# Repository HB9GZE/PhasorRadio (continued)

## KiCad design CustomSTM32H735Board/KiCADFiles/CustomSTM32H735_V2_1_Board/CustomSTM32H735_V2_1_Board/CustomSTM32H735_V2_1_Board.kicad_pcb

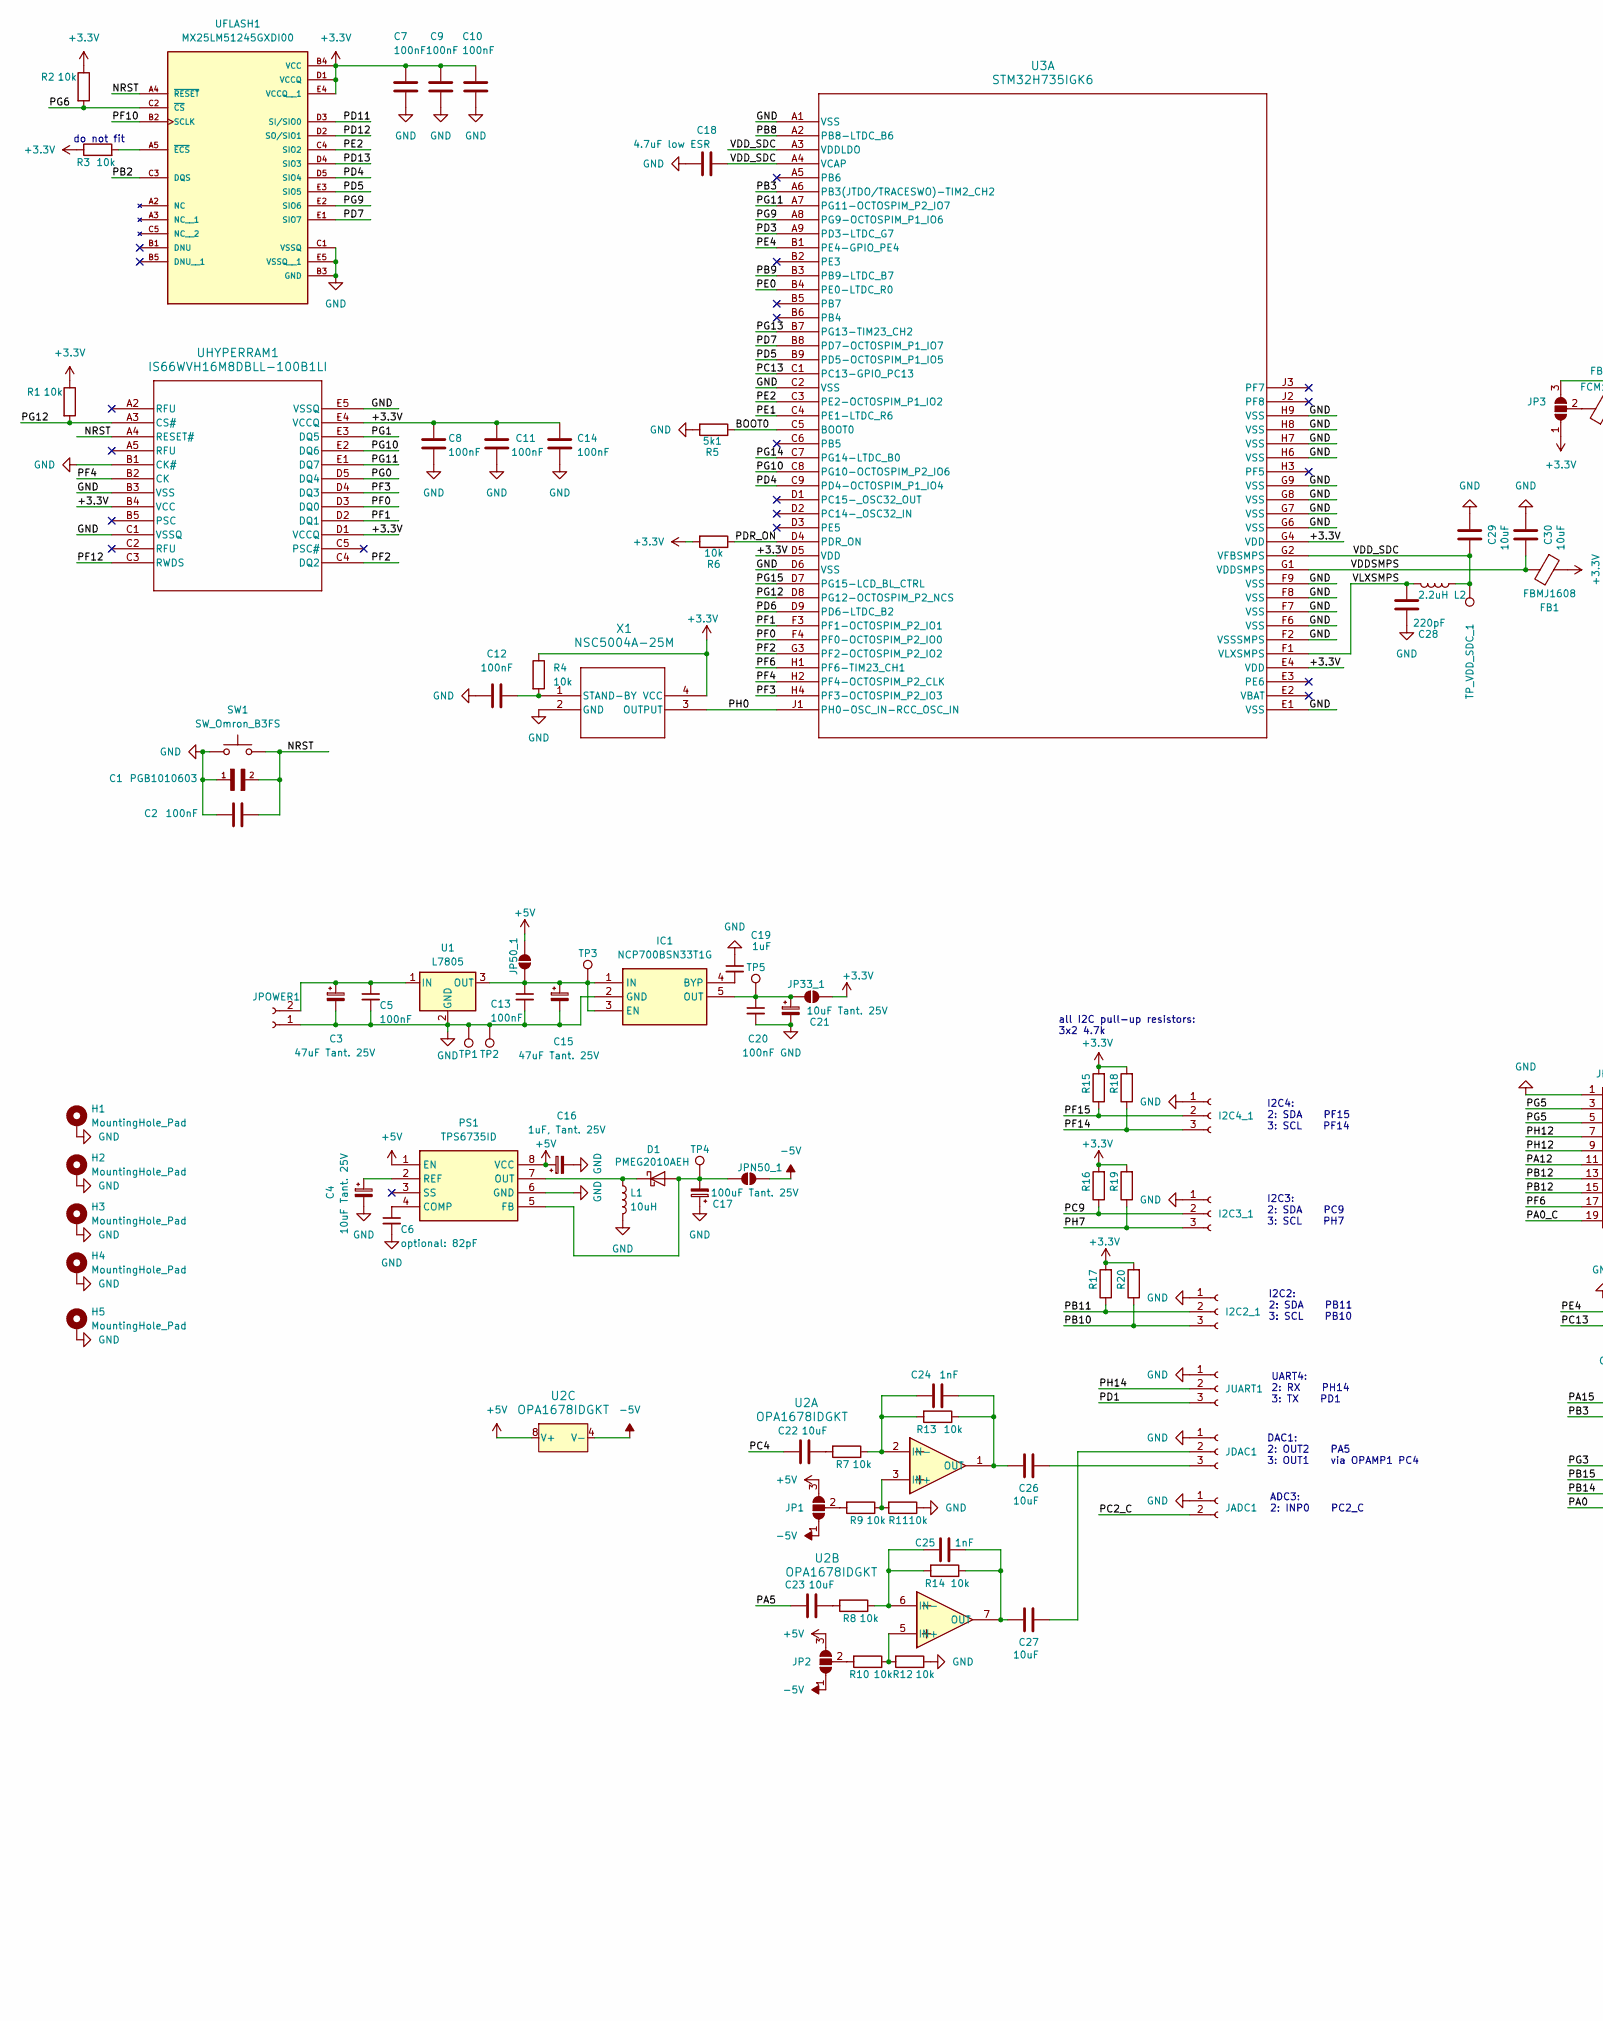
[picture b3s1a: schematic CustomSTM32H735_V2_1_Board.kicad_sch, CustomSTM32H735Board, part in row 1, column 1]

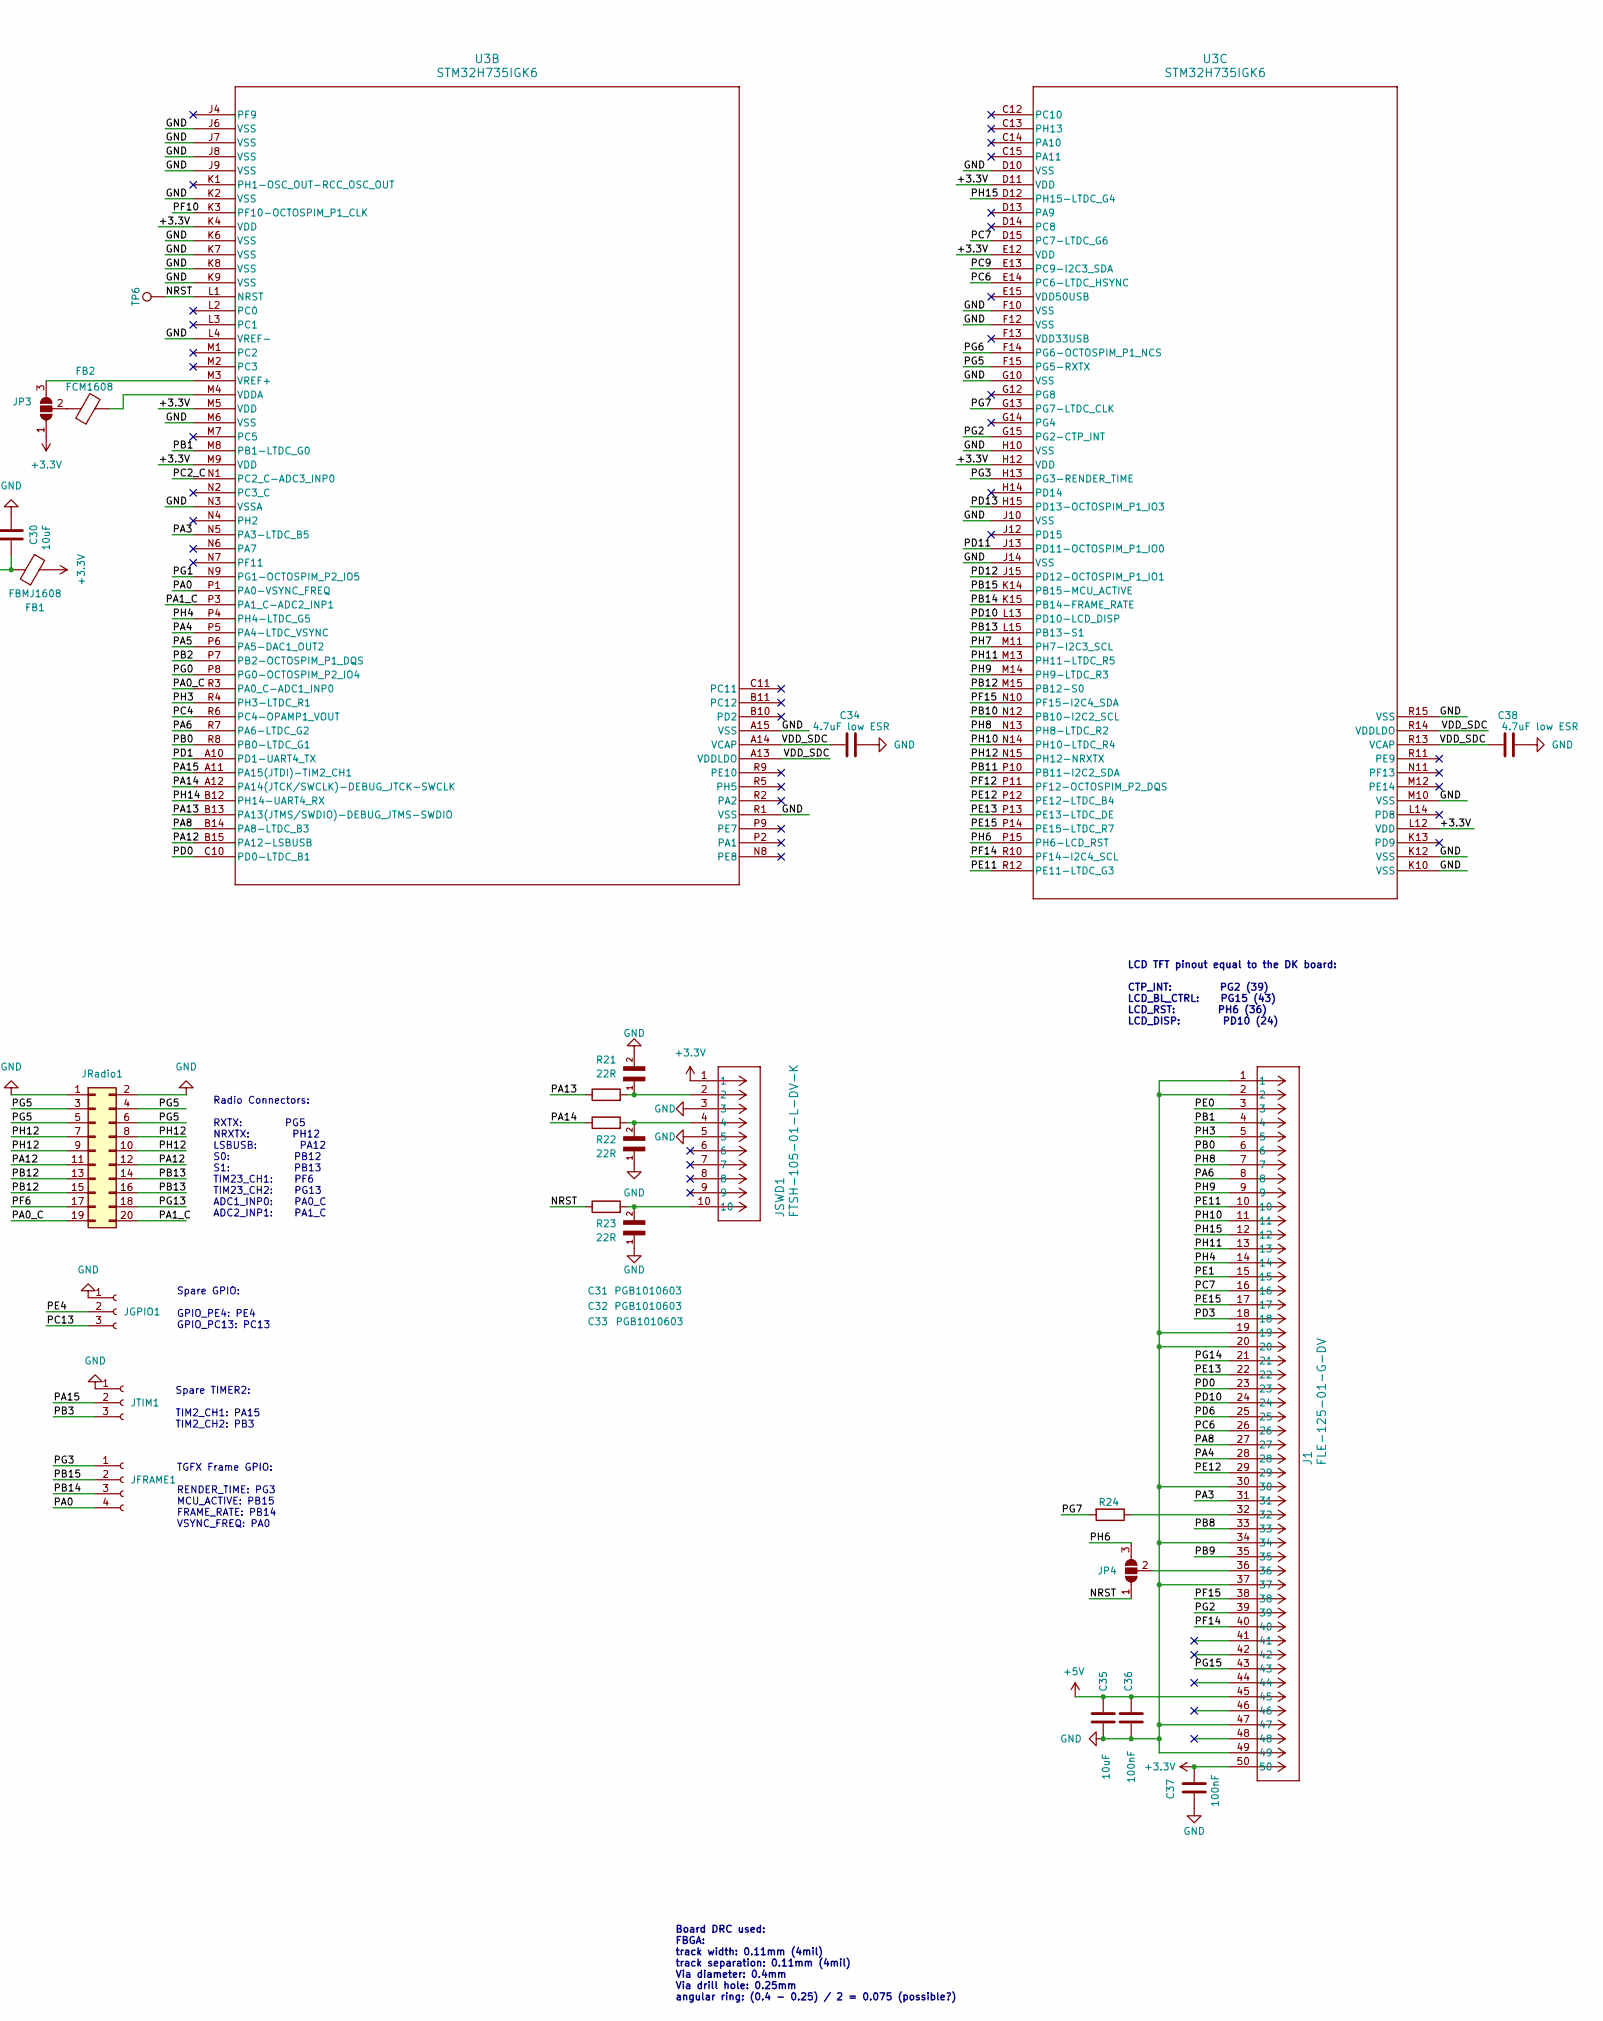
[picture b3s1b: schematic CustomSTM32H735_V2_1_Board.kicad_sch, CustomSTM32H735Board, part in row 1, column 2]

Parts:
C1, C31, C32, C33: PGB1010603; C_0603_1608Metric
C2, C5, C7, C8, C9, C10, C11, C12, C13, C14, C20, C36, C37: 100nF; C_0805_2012Metric_Pad1.18x1.45mm_HandSolder
C3, C15: 47uF Tant. 25V; CP_EIA-6032-20_AVX-F_Pad2.25x2.35mm_HandSolder
C4, C21: 10uF Tant. 25V; CP_EIA-6032-20_AVX-F_Pad2.25x2.35mm_HandSolder
C6: optional: 82pF; C_0805_2012Metric_Pad1.18x1.45mm_HandSolder
C16: 1uF, Tant. 25V; CP_EIA-6032-20_AVX-F_Pad2.25x2.35mm_HandSolder
C17: 100uF Tant. 25V; CP_EIA-6032-20_AVX-F_Pad2.25x2.35mm_HandSolder
C18, C34, C38: 4.7uF low ESR; C_0805_2012Metric_Pad1.18x1.45mm_HandSolder
C19: 1uF; C_0805_2012Metric_Pad1.18x1.45mm_HandSolder
C22, C23, C26, C27, C29, C30, C35: 10uF; C_0805_2012Metric_Pad1.18x1.45mm_HandSolder
C24, C25: 1nF; C_0805_2012Metric_Pad1.18x1.45mm_HandSolder
C28: 220pF; C_0805_2012Metric_Pad1.18x1.45mm_HandSolder
D1: PMEG2010AEH; D_SOD-123F
FB1: FBMJ1608; L_0603_1608Metric_Pad1.05x0.95mm_HandSolder
FB2: FCM1608; L_0603_1608Metric_Pad1.05x0.95mm_HandSolder
H1, H2, H3, H4, H5: MountingHole_Pad; MountingHole_3.2mm_M3_Pad_TopBottom
I2C2_1, I2C3_1, I2C4_1: Conn_01x03_Socket; JST_XH_B3B-XH-A_1x03_P2.50mm_Vertical
IC1: NCP700BSN33T1G; SOT95P275X120-5N; Manufacturer_Part_Number NCP700BSN33T1G; Mouser Part Number 863-NCP700BSN33T1G
J1: FLE-125-01-G-DV; CON50_2X25_UF_FLE_SAI
JADC1: Conn_01x02_Socket; JST_XH_B2B-XH-A_1x02_P2.50mm_Vertical
JDAC1: Conn_01x03_Socket; JST_XH_B3B-XH-A_1x03_P2.50mm_Vertical
JFRAME1: Conn_01x04_Socket; JST_XH_B4B-XH-A_1x04_P2.50mm_Vertical
JGPIO1: Conn_01x03_Socket; JST_XH_B3B-XH-A_1x03_P2.50mm_Vertical
JP1, JP2, JP3, JP4: SolderJumper_3_Open; SolderJumper-3_P1.3mm_Open_Pad1.0x1.5mm_NumberLabels
JP33_1, JP50_1: SolderJumper_2_Open; SolderJumper-2_P1.3mm_Open_Pad1.0x1.5mm
JPN50_1: SolderJumper_2_Open; SolderJumper-2_P1.3mm_Open_Pad1.0x1.5mm
JPOWER1: Conn_01x02_Socket; JST_XH_B2B-XH-A_1x02_P2.50mm_Vertical
JRadio1: Conn_02x10_Odd_Even; IDC-Header_2x10_P2.54mm_Vertical
JSWD1: FTSH-105-01-L-DV-K; CON10_2X5_DUK_FTSH_SAI-M
JTIM1: Conn_01x03_Socket; JST_XH_B3B-XH-A_1x03_P2.50mm_Vertical
JUART1: Conn_01x03_Socket; JST_XH_B3B-XH-A_1x03_P2.50mm_Vertical
L1: 10uH; L_1812_4532Metric_Pad1.30x3.40mm_HandSolder
L2: 2.2uH; L_Murata_DFE201610P
PS1: TPS6735ID; SOIC127P600X175-8N; Manufacturer_Part_Number TPS6735ID; Mouser Part Number 595-TPS6735ID
R1, R2, R3, R4, R6, R7, R8, R9, R10, R11, R12, R13, R14: 10k; R_0805_2012Metric_Pad1.20x1.40mm_HandSolder
R5: 5k1; R_0805_2012Metric_Pad1.20x1.40mm_HandSolder
R15, R16, R17, R18, R19, R20: 4.7k; R_0805_2012Metric_Pad1.20x1.40mm_HandSolder
R21, R22, R23: 22R; R_0805_2012Metric_Pad1.20x1.40mm_HandSolder
R24: 0R; R_0805_2012Metric_Pad1.20x1.40mm_HandSolder
SW1: SW_Omron_B3FS; SW_SPST_Omron_B3FS-100xP
TP1, TP2, TP3, TP4, TP5, TP6: TestPoint; Pin_D0.7mm_L6.5mm_W1.8mm_FlatFork
TP_VDD_SDC_1: TestPoint; Pin_D0.7mm_L6.5mm_W1.8mm_FlatFork
U1: L7805; TO-220-3_Horizontal_TabDown_GND_Pad
U2: OPA1678IDGKT; OPA1678_L
U3: STM32H735IGK6; BGA_735IGK6_STM
UFLASH1: MX25LM51245GXDI00; BGA24C100P5X5_600X800X120; PARTREV 1.1
UHYPERRAM1: IS66WVH16M8DBLL-100B1LI; TFBGA24_6X8_ISI
X1: NSC5004A-25M; NSC5004_NDK

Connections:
+3.3V: C7.1, C8.1, C9.1, C10.1, C11.1, C14.1, C37.1, FB1.1, J1.50, JP3.1 (A), JP33_1.2 (B), JSWD1.1, R1.1, R2.1, R3.1, R4.1, R6.2, R15.2, R16.2, R17.2, R18.2, R19.2, R20.2, U3.D5 (VDD), U3.D11 (VDD), U3.E4 (VDD), U3.E12 (VDD), U3.G4 (VDD), U3.H12 (VDD), U3.K4 (VDD), U3.L12 (VDD), U3.M5 (VDD), U3.M9 (VDD), UFLASH1.B4 (VCC), UFLASH1.D1 (VCCQ), UFLASH1.E4 (VCCQ__1), UHYPERRAM1.B4 (VCC), UHYPERRAM1.D1 (VCCQ), UHYPERRAM1.E4 (VCCQ), X1.4 (VCC)
+5V: C16.1, C35.1, C36.1, J1.45, JP1.3 (B), JP2.3 (B), JP50_1.2 (B), PS1.1 (EN), PS1.8 (VCC), U2.8 (V+)
-5V: JP1.1 (A), JP2.1 (A), JPN50_1.2 (B), U2.4 (V-)
/BOOT0: R5.1, U3.C5 (BOOT0)
/NRST: C1.2, C2.1, JP4.1 (A), R23.1, SW1.2, TP6.1, U3.L1 (NRST), UFLASH1.A4 (~RESET), UHYPERRAM1.A4 (RESET#)
/PA0: JFRAME1.4, U3.P1 (PA0-VSYNC_FREQ)
/PA0_C: JRadio1.19, U3.R3 (PA0_C-ADC1_INP0)
/PA1_C: JRadio1.20, U3.P3 (PA1_C-ADC2_INP1)
/PA3: J1.31, U3.N5 (PA3-LTDC_B5)
/PA4: J1.28, U3.P5 (PA4-LTDC_VSYNC)
/PA5: C23.1, U3.P6 (PA5-DAC1_OUT2)
/PA6: J1.8, U3.R7 (PA6-LTDC_G2)
/PA8: J1.27, U3.B14 (PA8-LTDC_B3)
/PA12: JRadio1.11, JRadio1.12, U3.B15 (PA12-LSBUSB)
/PA13: R21.1, U3.B13 (PA13(JTMS/SWDIO)-DEBUG_JTMS-SWDIO)
/PA14: R22.1, U3.A12 (PA14(JTCK/SWCLK)-DEBUG_JTCK-SWCLK)
/PA15: JTIM1.2, U3.A11 (PA15(JTDI)-TIM2_CH1)
/PB0: J1.6, U3.R8 (PB0-LTDC_G1)
/PB1: J1.4, U3.M8 (PB1-LTDC_G0)
/PB2: U3.P7 (PB2-OCTOSPIM_P1_DQS), UFLASH1.C3 (DQS)
/PB3: JTIM1.3, U3.A6 (PB3(JTDO/TRACESWO)-TIM2_CH2)
/PB8: J1.33, U3.A2 (PB8-LTDC_B6)
/PB9: J1.35, U3.B3 (PB9-LTDC_B7)
/PB10: I2C2_1.3, R20.1, U3.N12 (PB10-I2C2_SCL)
/PB11: I2C2_1.2, R17.1, U3.P10 (PB11-I2C2_SDA)
/PB12: JRadio1.13, JRadio1.15, U3.M15 (PB12-S0)
/PB13: JRadio1.14, JRadio1.16, U3.L15 (PB13-S1)
/PB14: JFRAME1.3, U3.K15 (PB14-FRAME_RATE)
/PB15: JFRAME1.2, U3.K14 (PB15-MCU_ACTIVE)
/PC2_C: JADC1.2, U3.N1 (PC2_C-ADC3_INP0)
/PC4: C22.1, U3.R6 (PC4-OPAMP1_VOUT)
/PC6: J1.26, U3.E14 (PC6-LTDC_HSYNC)
/PC7: J1.16, U3.D15 (PC7-LTDC_G6)
/PC9: I2C3_1.2, R16.1, U3.E13 (PC9-I2C3_SDA)
/PC13: JGPIO1.3, U3.C1 (PC13-GPIO_PC13)
/PD0: J1.23, U3.C10 (PD0-LTDC_B1)
/PD1: JUART1.3, U3.A10 (PD1-UART4_TX)
/PD3: J1.18, U3.A9 (PD3-LTDC_G7)
/PD4: U3.C9 (PD4-OCTOSPIM_P1_IO4), UFLASH1.D5 (SIO4)
/PD5: U3.B9 (PD5-OCTOSPIM_P1_IO5), UFLASH1.E3 (SIO5)
/PD6: J1.25, U3.D9 (PD6-LTDC_B2)
/PD7: U3.B8 (PD7-OCTOSPIM_P1_IO7), UFLASH1.E1 (SIO7)
/PD10: J1.24, U3.L13 (PD10-LCD_DISP)
/PD11: U3.J13 (PD11-OCTOSPIM_P1_IO0), UFLASH1.D3 (SI/SIO0)
/PD12: U3.J15 (PD12-OCTOSPIM_P1_IO1), UFLASH1.D2 (SO/SIO1)
/PD13: U3.H15 (PD13-OCTOSPIM_P1_IO3), UFLASH1.D4 (SIO3)
/PDR_ON: R6.1, U3.D4 (PDR_ON)
/PE0: J1.3, U3.B4 (PE0-LTDC_R0)
/PE1: J1.15, U3.C4 (PE1-LTDC_R6)
/PE2: U3.C3 (PE2-OCTOSPIM_P1_IO2), UFLASH1.C4 (SIO2)
/PE4: JGPIO1.2, U3.B1 (PE4-GPIO_PE4)
/PE11: J1.10, U3.R12 (PE11-LTDC_G3)
/PE12: J1.29, U3.P12 (PE12-LTDC_B4)
/PE13: J1.22, U3.P13 (PE13-LTDC_DE)
/PE15: J1.17, U3.P14 (PE15-LTDC_R7)
/PF0: U3.F4 (PF0-OCTOSPIM_P2_IO0), UHYPERRAM1.D3 (DQ0)
/PF1: U3.F3 (PF1-OCTOSPIM_P2_IO1), UHYPERRAM1.D2 (DQ1)
/PF2: U3.G3 (PF2-OCTOSPIM_P2_IO2), UHYPERRAM1.C4 (DQ2)
/PF3: U3.H4 (PF3-OCTOSPIM_P2_IO3), UHYPERRAM1.D4 (DQ3)
/PF4: U3.H2 (PF4-OCTOSPIM_P2_CLK), UHYPERRAM1.B2 (CK)
/PF6: JRadio1.17, U3.H1 (PF6-TIM23_CH1)
/PF10: U3.K3 (PF10-OCTOSPIM_P1_CLK), UFLASH1.B2 (SCLK)
/PF12: U3.P11 (PF12-OCTOSPIM_P2_DQS), UHYPERRAM1.C3 (RWDS)
/PF14: I2C4_1.3, J1.40, R18.1, U3.R10 (PF14-I2C4_SCL)
/PF15: I2C4_1.2, J1.38, R15.1, U3.N10 (PF15-I2C4_SDA)
/PG0: U3.P8 (PG0-OCTOSPIM_P2_IO4), UHYPERRAM1.D5 (DQ4)
/PG1: U3.N9 (PG1-OCTOSPIM_P2_IO5), UHYPERRAM1.E3 (DQ5)
/PG2: J1.39, U3.G15 (PG2-CTP_INT)
/PG3: JFRAME1.1, U3.H13 (PG3-RENDER_TIME)
/PG5: JRadio1.3, JRadio1.4, JRadio1.5, JRadio1.6, U3.F15 (PG5-RXTX)
/PG6: R2.2, U3.F14 (PG6-OCTOSPIM_P1_NCS), UFLASH1.C2 (~CS)
/PG7: R24.2, U3.G13 (PG7-LTDC_CLK)
/PG9: U3.A8 (PG9-OCTOSPIM_P1_IO6), UFLASH1.E2 (SIO6)
/PG10: U3.C8 (PG10-OCTOSPIM_P2_IO6), UHYPERRAM1.E2 (DQ6)
/PG11: U3.A7 (PG11-OCTOSPIM_P2_IO7), UHYPERRAM1.E1 (DQ7)
/PG12: R1.2, U3.D8 (PG12-OCTOSPIM_P2_NCS), UHYPERRAM1.A3 (CS#)
/PG13: JRadio1.18, U3.B7 (PG13-TIM23_CH2)
/PG14: J1.21, U3.C7 (PG14-LTDC_B0)
/PG15: J1.43, U3.D7 (PG15-LCD_BL_CTRL)
/PH0: U3.J1 (PH0-OSC_IN-RCC_OSC_IN), X1.3 (OUTPUT)
/PH3: J1.5, U3.R4 (PH3-LTDC_R1)
/PH4: J1.14, U3.P4 (PH4-LTDC_G5)
/PH6: JP4.3 (B), U3.P15 (PH6-LCD_RST)
/PH7: I2C3_1.3, R19.1, U3.M11 (PH7-I2C3_SCL)
/PH8: J1.7, U3.N13 (PH8-LTDC_R2)
/PH9: J1.9, U3.M14 (PH9-LTDC_R3)
/PH10: J1.11, U3.N14 (PH10-LTDC_R4)
/PH11: J1.13, U3.M13 (PH11-LTDC_R5)
/PH12: JRadio1.7, JRadio1.8, JRadio1.9, JRadio1.10, U3.N15 (PH12-NRXTX)
/PH14: JUART1.2, U3.B12 (PH14-UART4_RX)
/PH15: J1.12, U3.D12 (PH15-LTDC_G4)
/VDDSMPS: C30.1, FB1.2, U3.G1 (VDDSMPS)
/VDD_SDC: C18.2, C29.1, C34.2, C38.2, L2.1, TP_VDD_SDC_1.1, U3.A3 (VDDLDO), U3.A4 (VCAP), U3.A13 (VDDLDO), U3.A14 (VCAP), U3.G2 (VFBSMPS), U3.R13 (VCAP), U3.R14 (VDDLDO); also elsewhere on the board
/VLXSMPS: C28.2, L2.2, U3.F1 (VLXSMPS)
GND: C1.1, C2.2, C3.2, C4.2, C5.2, C6.2, C7.2, C8.2, C9.2, C10.2, C11.2, C12.1, C13.2, C14.2, C15.2, C16.2, C17.1, C18.1, C19.1, C20.2, C21.2, C28.1, C29.2, C30.2, C31.2, C32.1, C33.1, C34.1, C35.2, C36.2, C37.2, C38.1, H1.1, H2.1, H3.1, H4.1, H5.1, I2C2_1.1, I2C3_1.1, I2C4_1.1, IC1.2 (GND), J1.1, J1.2, J1.19, J1.20, J1.30, J1.34, J1.37, J1.47, J1.49, JADC1.1, JDAC1.1, JGPIO1.1, JPOWER1.1, JRadio1.1, JRadio1.2, JSWD1.3, JSWD1.5, JTIM1.1, JUART1.1, L1.2, PS1.6 (GND), R5.2, R11.1, R12.1, SW1.1, TP1.1, TP2.1, U1.2 (GND), U1.4, U3.A1 (VSS), U3.A15 (VSS), U3.C2 (VSS), U3.D6 (VSS), U3.D10 (VSS), U3.E1 (VSS), U3.F2 (VSSSMPS), U3.F6 (VSS), U3.F7 (VSS), U3.F8 (VSS), U3.F9 (VSS), U3.F10 (VSS), U3.F12 (VSS), U3.G6 (VSS), U3.G7 (VSS), U3.G8 (VSS), U3.G9 (VSS), U3.G10 (VSS), U3.H6 (VSS), U3.H7 (VSS), U3.H8 (VSS), U3.H9 (VSS), U3.H10 (VSS), U3.J6 (VSS), U3.J7 (VSS), U3.J8 (VSS), U3.J9 (VSS), U3.J10 (VSS), U3.J14 (VSS), U3.K2 (VSS), U3.K6 (VSS), U3.K7 (VSS), U3.K8 (VSS), U3.K9 (VSS), U3.K10 (VSS), U3.K12 (VSS), U3.L4 (VREF-), U3.M6 (VSS), U3.M10 (VSS), U3.N3 (VSSA), U3.R1 (VSS), U3.R15 (VSS), UFLASH1.B3 (GND), UFLASH1.C1 (VSSQ), UFLASH1.E5 (VSSQ__1), UHYPERRAM1.B1 (CK#), UHYPERRAM1.B3 (VSS), UHYPERRAM1.C1 (VSSQ), UHYPERRAM1.E5 (VSSQ), X1.2 (GND)
unnamed: C22.2, R7.2
unnamed: C23.2, R8.2
unnamed: C31.1, JSWD1.2, R21.2
unnamed: C32.2, JSWD1.4, R22.2
unnamed: C33.2, JSWD1.10, R23.2
unnamed: C17.2, D1.2 (A), JPN50_1.1 (A), PS1.5 (FB), TP4.1
unnamed: D1.1 (K), L1.1, PS1.7 (OUT)
unnamed: C19.2, IC1.4 (BYP)
unnamed: C13.1, C15.1, IC1.1 (IN), IC1.3 (EN), JP50_1.1 (A), TP3.1, U1.3 (OUT)
unnamed: C20.1, C21.1, IC1.5 (OUT), JP33_1.1 (A), TP5.1
unnamed: J1.32, R24.1
unnamed: C27.2, JDAC1.2
unnamed: C26.2, JDAC1.3
unnamed: JP1.2 (C), R9.2
unnamed: JP2.2 (C), R10.2
unnamed: JP3.3 (B), U3.M3 (VREF+)
unnamed: FB2.1, JP3.2 (C)
unnamed: J1.36, JP4.2 (C)
unnamed: C3.1, C5.1, JPOWER1.2, U1.1 (IN)
unnamed: C6.1, PS1.4 (COMP)
unnamed: C4.1, PS1.2 (REF)
unnamed: R9.1, R11.2, U2.3 (IN+)
unnamed: C24.1, R7.1, R13.2, U2.2 (IN-)
unnamed: C24.2, C26.1, R13.1, U2.1 (OUT)
unnamed: R10.1, R12.2, U2.5 (IN+)
unnamed: C25.1, R8.1, R14.2, U2.6 (IN-)
unnamed: C25.2, C27.1, R14.1, U2.7 (OUT)
unnamed: FB2.2, U3.M4 (VDDA)
unnamed: R3.2, UFLASH1.A5 (~ECS)
unnamed: C12.2, R4.2, X1.1 (STAND-BY)

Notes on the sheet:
TGFX Frame GPIO: RENDER_TIME: PG3 MCU_ACTIVE: PB15 FRAME_RATE: PB14 VSYNC_FREQ: PA0
Spare TIMER2: TIM2_CH1: PA15 TIM2_CH2: PB3
DAC1: 2: OUT2 PA5 3: OUT1 via OPAMP1 PC4
Radio Connectors: RXTX: PG5 NRXTX: PH12 LSBUSB: PA12 S0: PB12 S1: PB13 TIM23_CH1: PF6 TIM23_CH2: PG13 ADC1_INP0: PA0_C ADC2_INP1: PA1_C
LCD TFT pinout equal to the DK board: CTP_INT: PG2 (39) LCD_BL_CTRL: PG15 (43) LCD_RST: PH6 (36) LCD_DISP: PD10 (24)
I2C2: 2: SDA PB11 3: SCL PB10
Spare GPIO: GPIO_PE4: PE4 GPIO_PC13: PC13
do not fit
UART4: 2: RX PH14 3: TX PD1
ADC3: 2: INP0 PC2_C
Board DRC used: FBGA: track width: 0.11mm (4mil) track separation: 0.11mm (4mil) Via diameter: 0.4mm Via drill hole: 0.25mm angular ring: (0.4 - 0.25) / 2 = 0.075 (possible?)
I2C3: 2: SDA PC9 3: SCL PH7
all I2C pull-up resistors: 3x2 4.7k
I2C4: 2: SDA PF15 3: SCL PF14

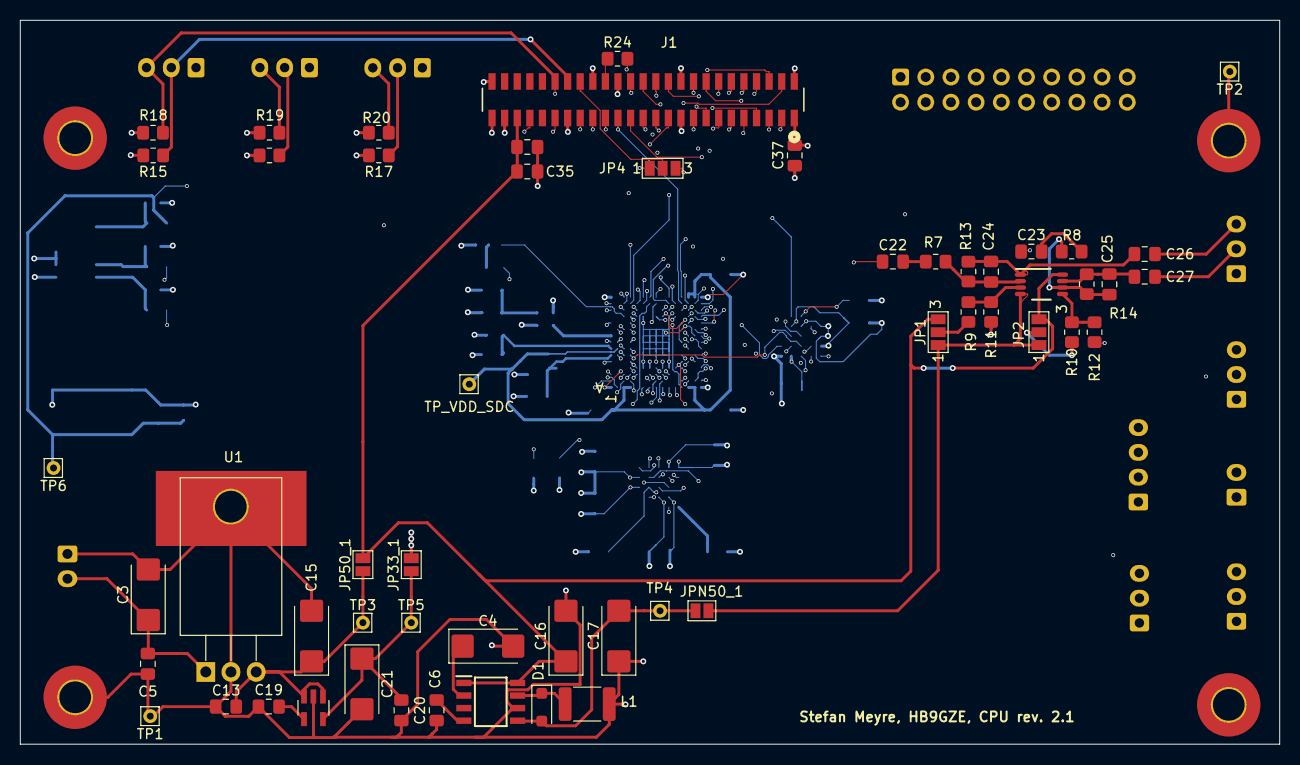
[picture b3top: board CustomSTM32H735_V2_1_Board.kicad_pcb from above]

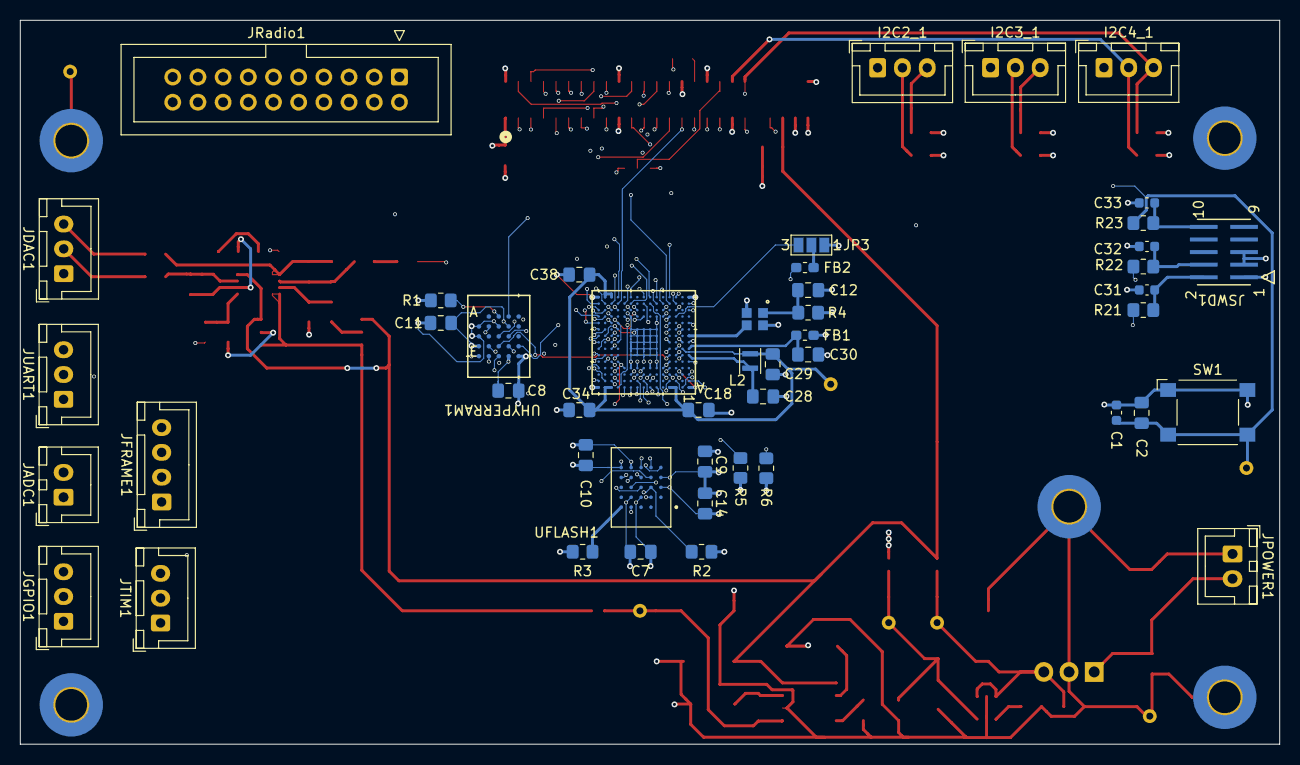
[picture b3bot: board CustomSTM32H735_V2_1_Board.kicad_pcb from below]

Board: 6 copper layers, 127.0 x 73.0 mm, 108 parts (48 on the bottom side), 125 nets.

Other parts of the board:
TP_VDD_SDC: TestPoint; Pin_D0.7mm_L6.5mm_W1.8mm_FlatFork

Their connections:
/VDD_SDC: TP_VDD_SDC.1; also elsewhere on the board
